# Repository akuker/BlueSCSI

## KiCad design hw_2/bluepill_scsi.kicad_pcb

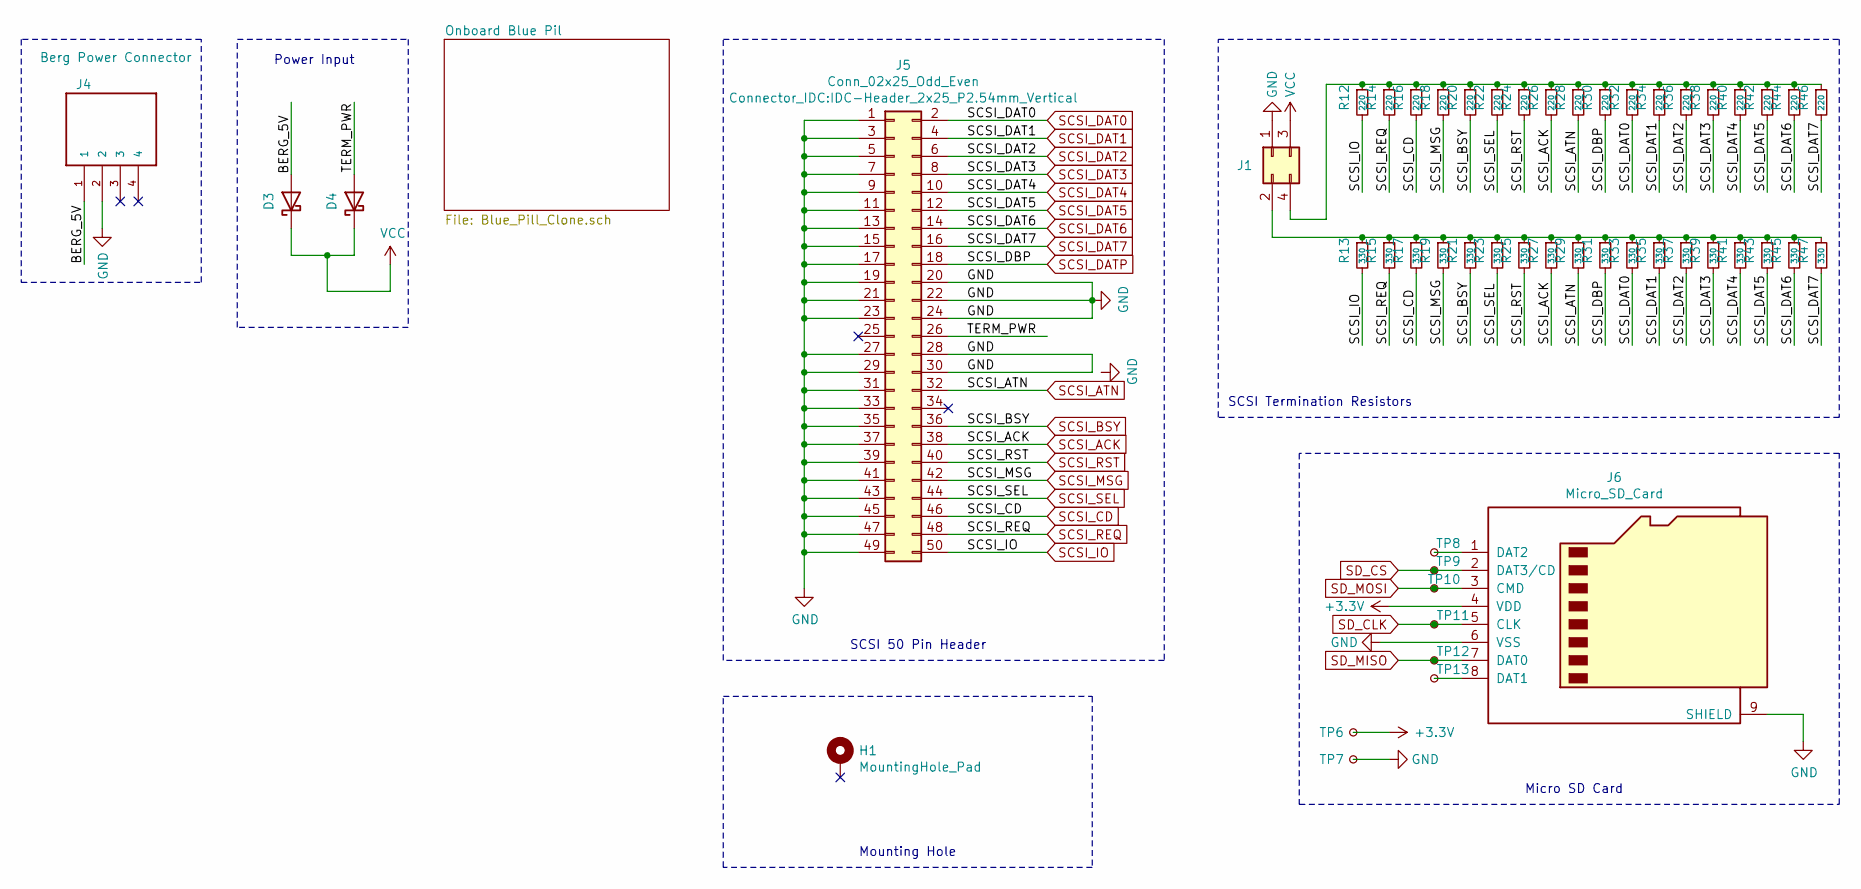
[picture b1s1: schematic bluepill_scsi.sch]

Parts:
D3, D4: D_Schottky; D_SOD-123; LCSC C8598
H1: MountingHole_Pad; MountingHole_2.7mm_M2.5
J1: Conn_02x02_Odd_Even; PinHeader_2x02_P2.54mm_Vertical
J4: Berg Power Connector; TE_171825-4
J5: Conn_02x25_Odd_Even; IDC-Header_2x25_P2.54mm_Vertical
J6: Micro_SD_Card; microSD_HC_Molex_104031-0811
R12, R14, R16, R18, R20, R22, R24, R26, R28, R30, R32, R34, R36, R38, R40, R42, R44, R46: 220; R_0603_1608Metric; LCSC C22962
R13, R15, R17, R19, R21, R23, R25, R27, R29, R31, R33, R35, R37, R39, R41, R43, R45, R47: 330; R_0603_1608Metric; LCSC C23138
TP6, TP7, TP8, TP9, TP10, TP11, TP12, TP13: TestPoint_Small; TestPoint_THTPad_D1.0mm_Drill0.5mm

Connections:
/BERG_5V: D3.2 (A), J4.1
/TERM_PWR: D4.2 (A), J5.26
GND: J1.1, J4.2, J5.1, J5.3, J5.5, J5.7, J5.9, J5.11, J5.13, J5.15, J5.17, J5.19, J5.20, J5.21, J5.22, J5.23, J5.24, J5.27, J5.28, J5.29, J5.30, J5.31, J5.33, J5.35, J5.37, J5.39, J5.41, J5.43, J5.45, J5.47, J5.49, J6.6 (VSS), J6.9 (SHIELD), TP7.1; also elsewhere on the board
unnamed: J1.2, R13.1, R15.1, R17.1, R19.1, R21.1, R23.1, R25.1, R27.1, R29.1, R31.1, R33.1, R35.1, R37.1, R39.1, R41.1, R43.1, R45.1, R47.1
unnamed: J1.4, R12.1, R14.1, R16.1, R18.1, R20.1, R22.1, R24.1, R26.1, R28.1, R30.1, R32.1, R34.1, R36.1, R38.1, R40.1, R42.1, R44.1, R46.1
unnamed: J6.1 (DAT2), TP8.1
unnamed: J6.8 (DAT1), TP13.1
SCSI_ACK: J5.38, R26.2, R27.2; also elsewhere on the board
SCSI_ATN: J5.32, R28.2, R29.2; also elsewhere on the board
SCSI_BSY: J5.36, R20.2, R21.2; also elsewhere on the board
SCSI_CD: J5.46, R16.2, R17.2; also elsewhere on the board
SCSI_DAT0: J5.2, R32.2, R33.2; also elsewhere on the board
SCSI_DAT1: J5.4, R34.2, R35.2; also elsewhere on the board
SCSI_DAT2: J5.6, R36.2, R37.2; also elsewhere on the board
SCSI_DAT3: J5.8, R38.2, R39.2; also elsewhere on the board
SCSI_DAT4: J5.10, R40.2, R41.2; also elsewhere on the board
SCSI_DAT5: J5.12, R42.2, R43.2; also elsewhere on the board
SCSI_DAT6: J5.14, R44.2, R45.2; also elsewhere on the board
SCSI_DAT7: J5.16, R46.2, R47.2; also elsewhere on the board
SCSI_DATP: J5.18, R30.2, R31.2; also elsewhere on the board
SCSI_IO: J5.50, R12.2, R13.2; also elsewhere on the board
SCSI_MSG: J5.42, R18.2, R19.2; also elsewhere on the board
SCSI_REQ: J5.48, R14.2, R15.2; also elsewhere on the board
SCSI_RST: J5.40, R24.2, R25.2; also elsewhere on the board
SCSI_SEL: J5.44, R22.2, R23.2; also elsewhere on the board
SD_CLK: J6.5 (CLK), TP11.1; also elsewhere on the board
SD_CS: J6.2 (DAT3/CD), TP9.1; also elsewhere on the board
SD_MISO: J6.7 (DAT0), TP12.1; also elsewhere on the board
SD_MOSI: J6.3 (CMD), TP10.1; also elsewhere on the board
VCC: D3.1 (K), D4.1 (K), J1.3; also elsewhere on the board

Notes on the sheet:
SCSI 50 Pin Header
Micro SD Card
Mounting Hole
SCSI Termination Resistors
Power Input

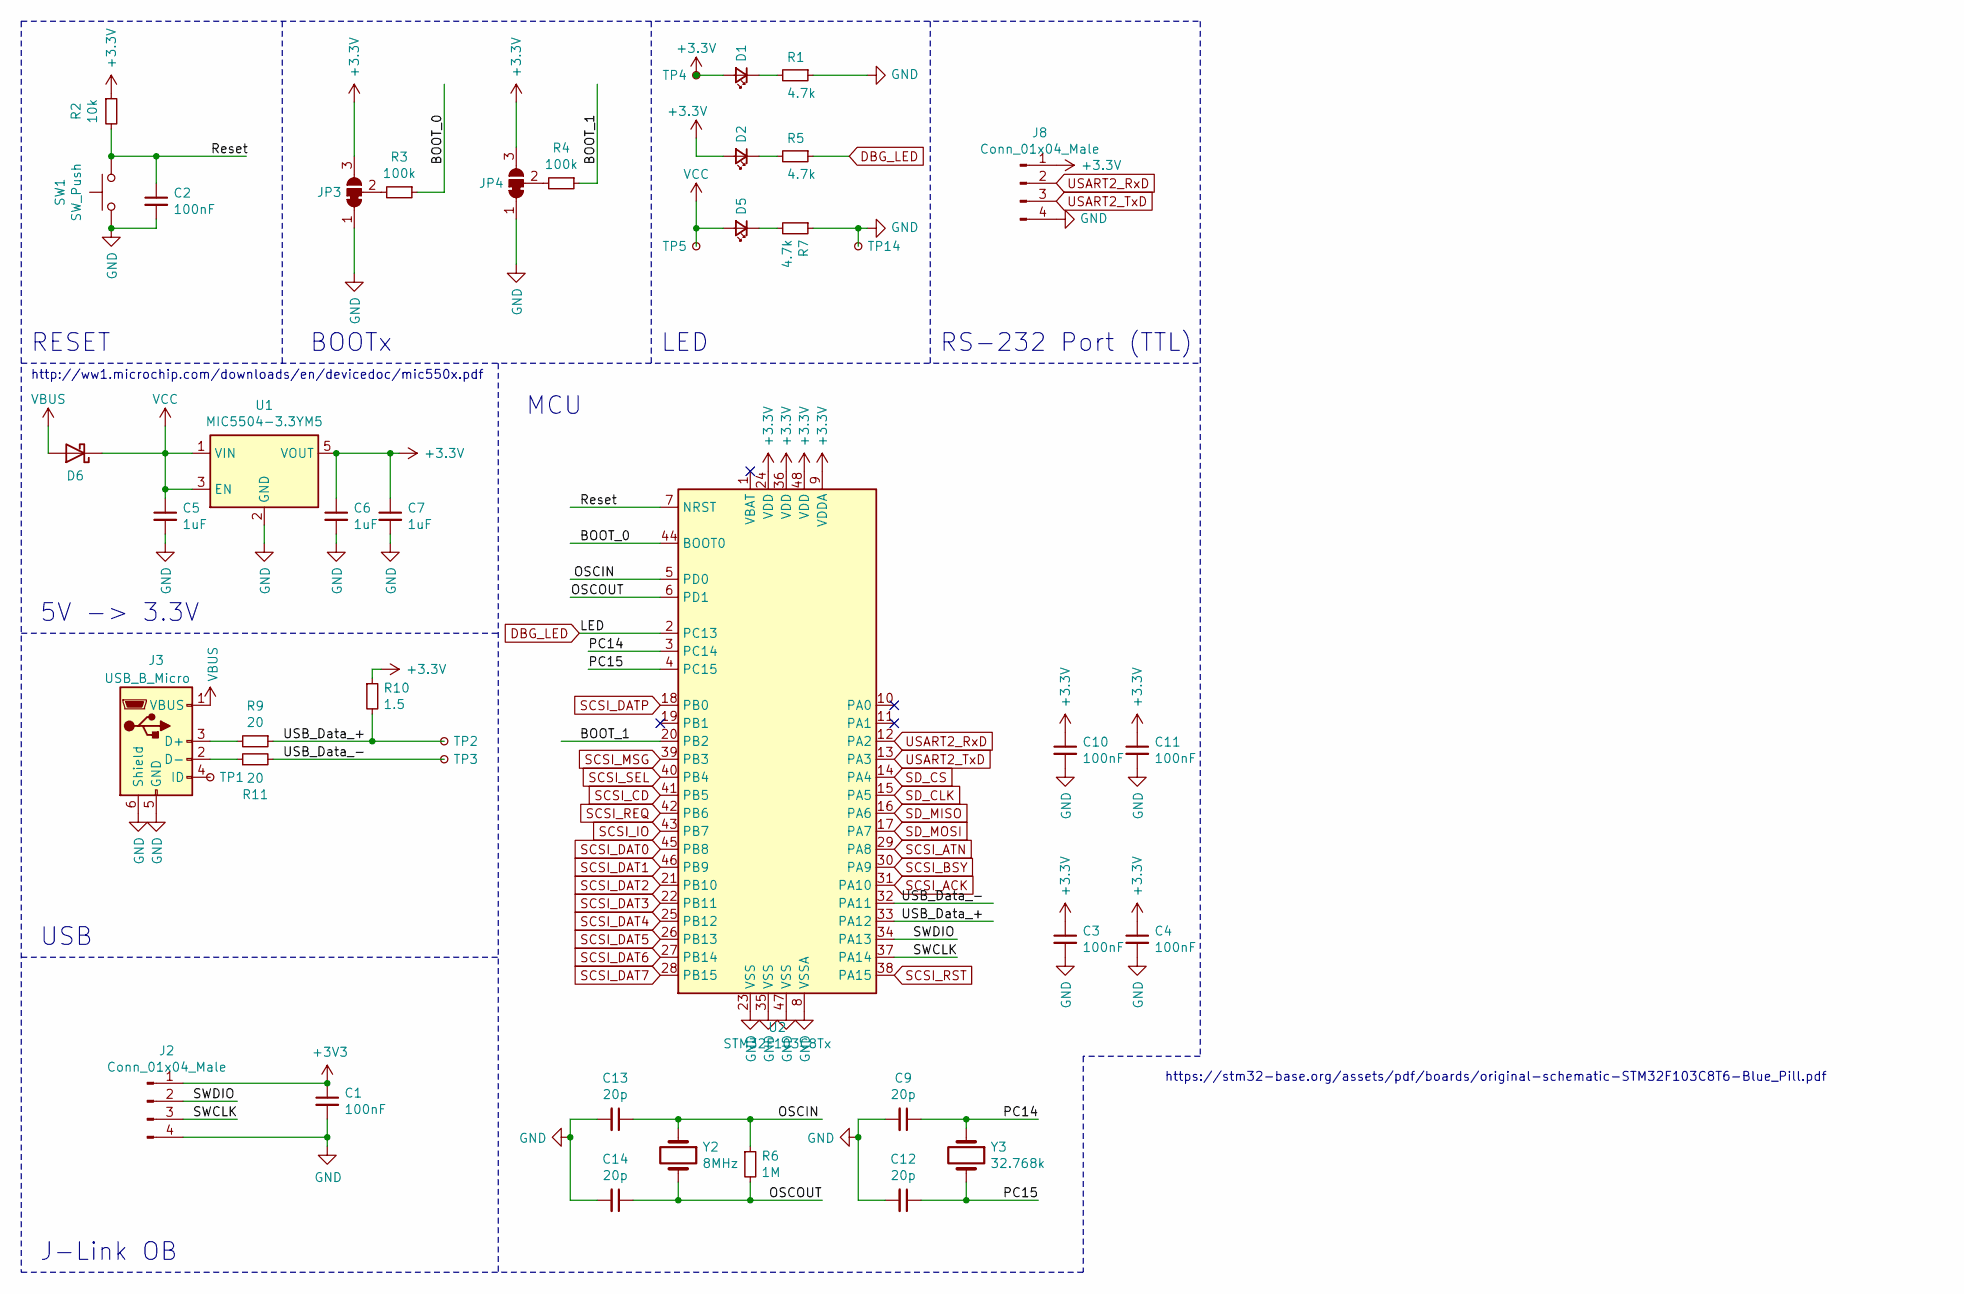
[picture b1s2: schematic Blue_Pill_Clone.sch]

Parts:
C1, C2, C3, C4, C10, C11: 100nF; C_0603_1608Metric; LCSC C14663
C5, C6, C7: 1uF; C_0603_1608Metric; LCSC C15849
C9, C12, C13, C14: 20p; C_0603_1608Metric; LCSC C1648
D1, D2, D5: LED_Small; LED_0603_1608Metric; LCSC C72043
D6: D_Schottky; D_SOD-123; LCSC C8598
J2, J8: Conn_01x04_Male; PinHeader_1x04_P2.54mm_Vertical
J3: USB_B_Micro; USB_Micro-B_Wuerth_629105150521
JP3, JP4: Jumper_3_Bridged12; SolderJumper-3_P1.3mm_Bridged12_RoundedPad1.0x1.5mm
R1, R5, R7: 4.7k; R_0603_1608Metric; LCSC C23162
R2: 10k; R_0603_1608Metric; LCSC C25804
R3, R4: 100k; R_0603_1608Metric; LCSC C25803
R6: 1M; R_0603_1608Metric; LCSC C22935
R9, R11: 20; R_0603_1608Metric; LCSC C22950
R10: 1.5; R_0603_1608Metric; LCSC C22843
SW1: SW_Push; SW_PUSH_6mm; LCSC C223748
TP1, TP2, TP3, TP4, TP5, TP14: TestPoint_Small; TestPoint_Pad_D1.5mm
U1: MIC5504-3.3YM5; SOT-23-5; LCSC C88419
U2: STM32F103C8Tx; LQFP-48_7x7mm_P0.5mm; LCSC C8734
Y2: 8MHz; Crystal_SMD_5032-2Pin_5.0x3.2mm; LCSC C115962
Y3: 32.768k; Crystal_SMD_3215-2Pin_3.2x1.5mm; LCSC C48615

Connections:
/Onboard Blue Pil/BOOT_0: R3.1, U2.44 (BOOT0)
/Onboard Blue Pil/BOOT_1: R4.1, U2.20 (PB2)
/Onboard Blue Pil/OSCIN: C13.1, R6.1, U2.5 (PD0), Y2.1
/Onboard Blue Pil/OSCOUT: C14.1, R6.2, U2.6 (PD1), Y2.2
/Onboard Blue Pil/PC14: C9.1, U2.3 (PC14), Y3.1
/Onboard Blue Pil/PC15: C12.1, U2.4 (PC15), Y3.2
/Onboard Blue Pil/Reset: C2.1, R2.2, SW1.2, U2.7 (NRST)
/Onboard Blue Pil/SWCLK: J2.3, U2.37 (PA14)
/Onboard Blue Pil/SWDIO: J2.2, U2.34 (PA13)
/Onboard Blue Pil/USB_Data_+: R9.1, R10.2, TP2.1, U2.33 (PA12)
/Onboard Blue Pil/USB_Data_-: R11.2, TP3.1, U2.32 (PA11)
DBG_LED: R5.1, U2.2 (PC13)
GND: C1.2, C2.2, C3.2, C4.2, C5.2, C6.2, C7.2, C9.2, C10.2, C11.2, C12.2, C13.2, C14.2, J2.4, J3.5 (GND), J3.6 (Shield), J8.4, JP3.1 (A), JP4.1 (A), R1.1, R7.1, SW1.1, TP14.1, U1.2 (GND), U2.8 (VSSA), U2.23 (VSS), U2.35 (VSS), U2.47 (VSS); also elsewhere on the board
unnamed: D1.1 (K), R1.2
unnamed: D2.1 (K), R5.2
unnamed: D5.1 (K), R7.2
unnamed: J3.2 (D-), R11.1
unnamed: J3.3 (D+), R9.2
unnamed: J3.4 (ID), TP1.1
unnamed: JP3.2 (C), R3.2
unnamed: JP4.2 (C), R4.2
SCSI_ACK: U2.31 (PA10); also elsewhere on the board
SCSI_ATN: U2.29 (PA8); also elsewhere on the board
SCSI_BSY: U2.30 (PA9); also elsewhere on the board
SCSI_CD: U2.41 (PB5); also elsewhere on the board
SCSI_DAT0: U2.45 (PB8); also elsewhere on the board
SCSI_DAT1: U2.46 (PB9); also elsewhere on the board
SCSI_DAT2: U2.21 (PB10); also elsewhere on the board
SCSI_DAT3: U2.22 (PB11); also elsewhere on the board
SCSI_DAT4: U2.25 (PB12); also elsewhere on the board
SCSI_DAT5: U2.26 (PB13); also elsewhere on the board
SCSI_DAT6: U2.27 (PB14); also elsewhere on the board
SCSI_DAT7: U2.28 (PB15); also elsewhere on the board
SCSI_DATP: U2.18 (PB0); also elsewhere on the board
SCSI_IO: U2.43 (PB7); also elsewhere on the board
SCSI_MSG: U2.39 (PB3); also elsewhere on the board
SCSI_REQ: U2.42 (PB6); also elsewhere on the board
SCSI_RST: U2.38 (PA15); also elsewhere on the board
SCSI_SEL: U2.40 (PB4); also elsewhere on the board
SD_CLK: U2.15 (PA5); also elsewhere on the board
SD_CS: U2.14 (PA4); also elsewhere on the board
SD_MISO: U2.16 (PA6); also elsewhere on the board
SD_MOSI: U2.17 (PA7); also elsewhere on the board
USART2_RxD: J8.2, U2.12 (PA2)
USART2_TxD: J8.3, U2.13 (PA3)
VBUS: D6.2 (A), J3.1 (VBUS)
VCC: C5.1, D5.2 (A), D6.1 (K), TP5.1, U1.1 (VIN), U1.3 (EN); also elsewhere on the board

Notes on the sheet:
https://stm32-base.org/assets/pdf/boards/original-schematic-STM32F103C8T6-Blue_Pill.pdf
RESET
BOOTx
LED
5V -> 3.3V
USB
J-Link OB
MCU
RS-232 Port (TTL)
http://ww1.microchip.com/downloads/en/devicedoc/mic550x.pdf

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
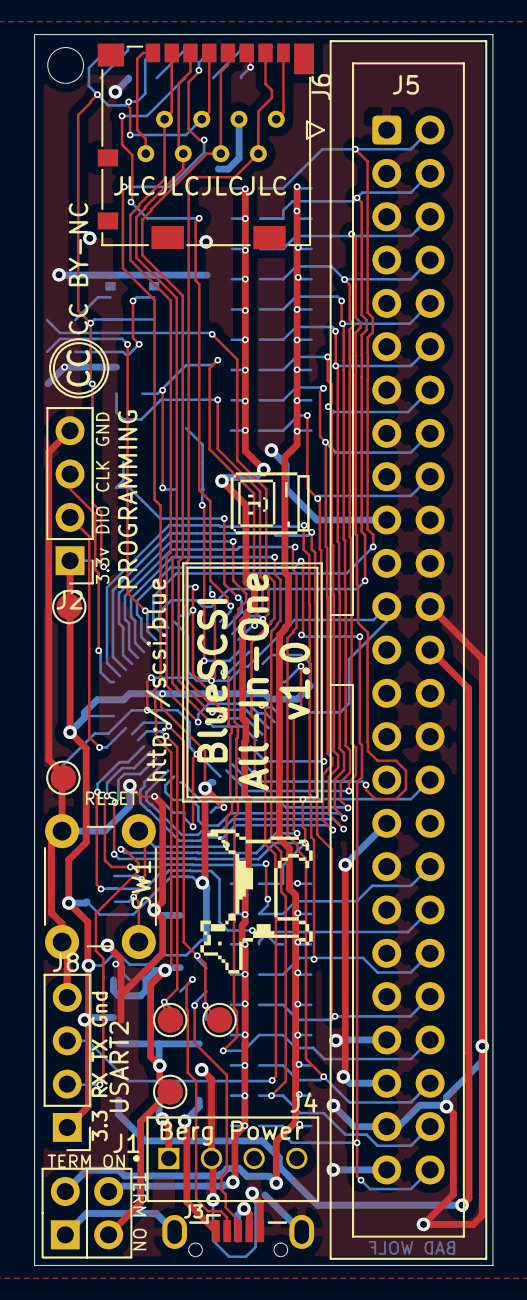
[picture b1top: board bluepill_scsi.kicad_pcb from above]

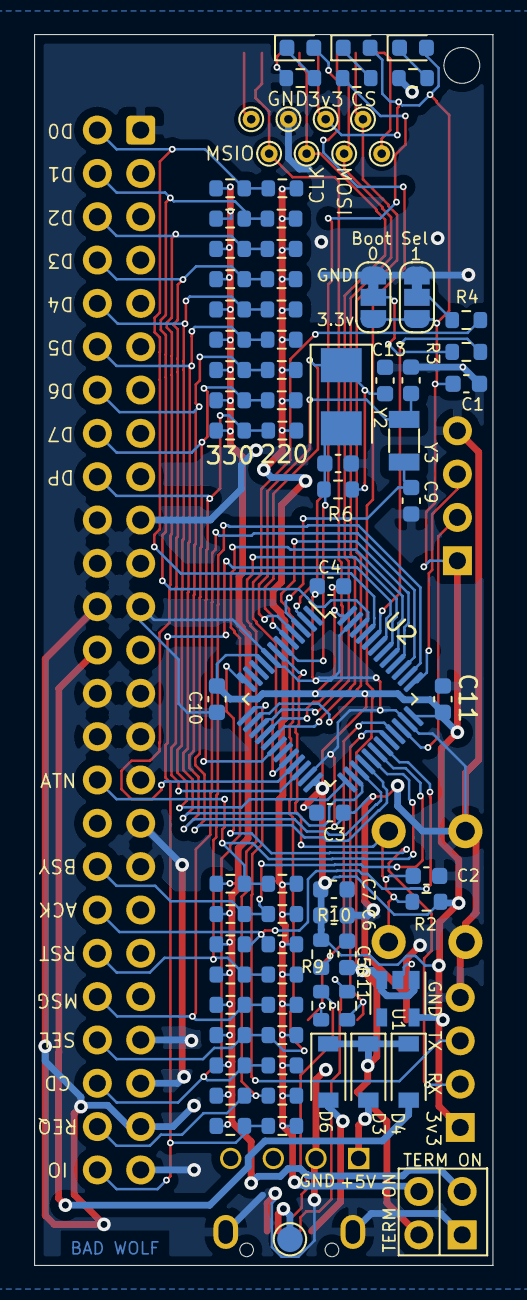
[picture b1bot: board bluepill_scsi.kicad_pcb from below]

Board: 2 copper layers, 26.9 x 72.2 mm, 93 parts (80 on the bottom side), 54 nets.

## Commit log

2021-05-18 Added rough cut of STM32
2021-05-19 Updated bluepill all-in-one
2021-05-19 As-ordered version
2021-05-20 Fixed resistor sizes. As-ordered Beta 3
2021-05-27 Fixes from Beta 3
2021-05-28 Fixes from integration. As-ordered 1.0
2021-06-06 smaller version
2021-07-06 Updated silkscreens
2021-07-07 Version 1.0 as ordered

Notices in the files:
hw_2/bluepill_scsi.kicad_pcb:
CC BY-NC
